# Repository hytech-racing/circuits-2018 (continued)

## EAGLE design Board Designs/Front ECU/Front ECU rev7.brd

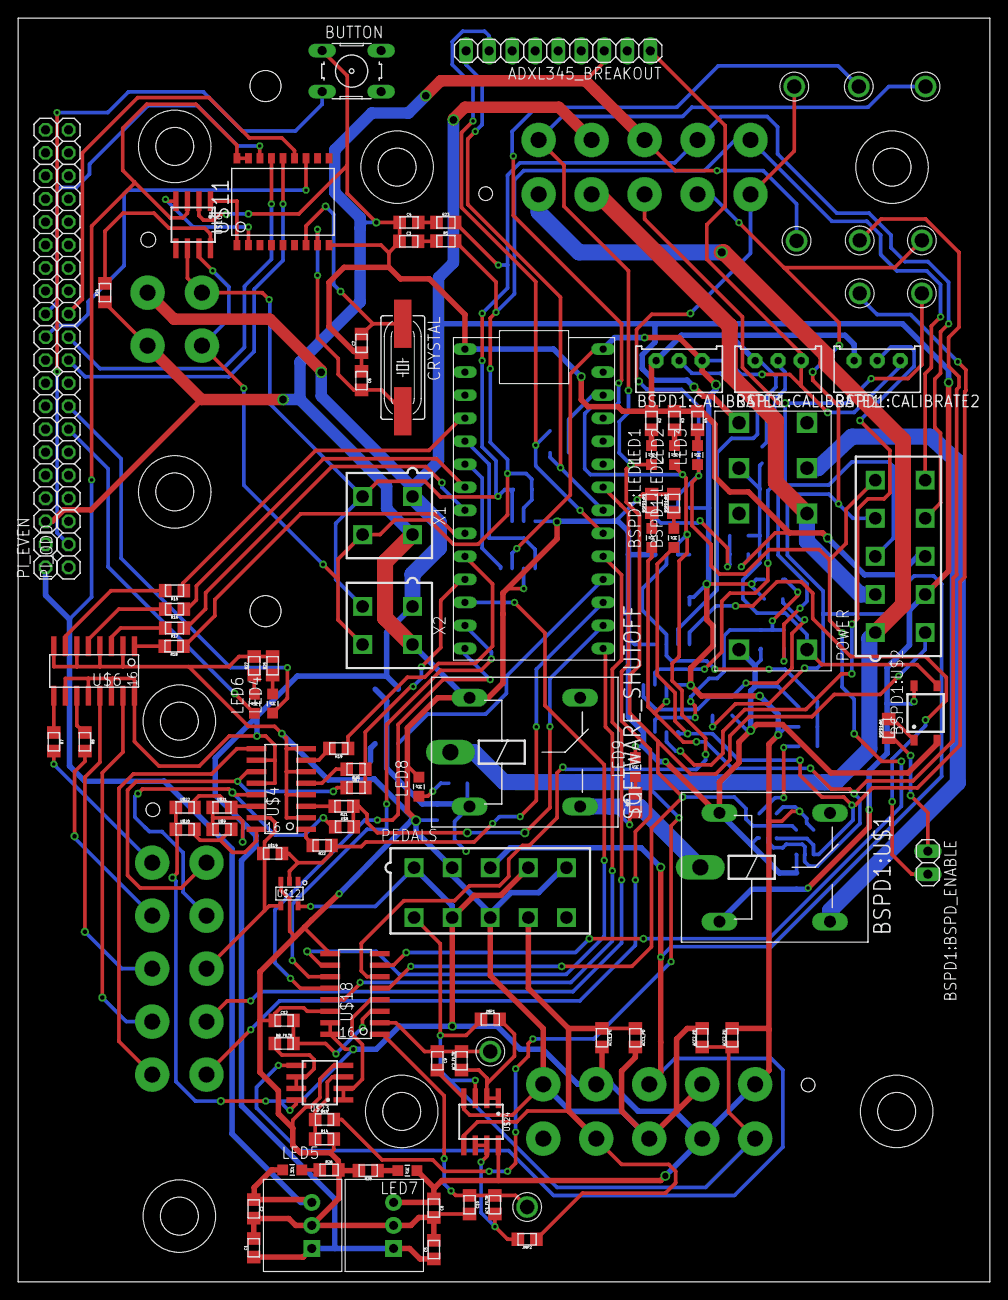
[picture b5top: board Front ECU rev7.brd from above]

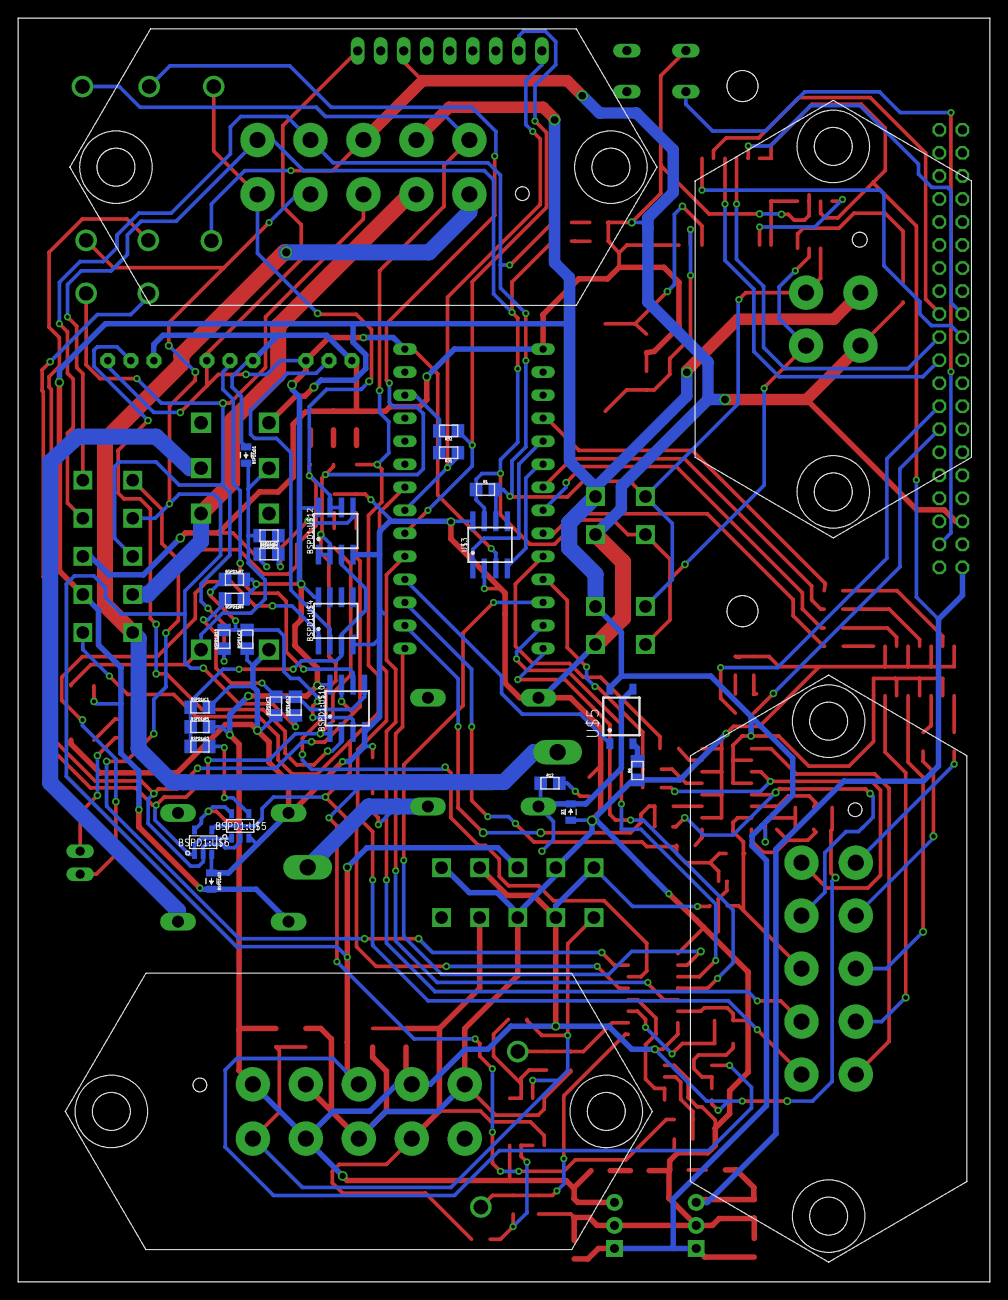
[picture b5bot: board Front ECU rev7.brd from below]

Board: 2 copper layers, 107.2 x 139.4 mm, 132 parts (30 on the bottom side), 107 nets.

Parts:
AC1_FILTR, AC2_FILTR: 510; 0805
ACC1_PD, ACC1_PU, ACC2_PD, ACC2_PU: 10k; 0805
ADXL345_BREAKOUT: 1X09
BR_FILTR: 100; 0805
BSPD1:BSPD_ENABLE: JUMPER; 1X02
BSPD1:C1: .47µ; 0805
BSPD1:C2, BSPD1:C3: 2.2µ; 0805
BSPD1:CALIBRATE1, BSPD1:CALIBRATE2, BSPD1:CALIBRATE3: TRIMPOT_3296
BSPD1:D1, BSPD1:D2: DIODE0805; 0805_D
BSPD1:LED1: RED; LED-805
BSPD1:LED2: YELLOW; LED-805
BSPD1:R1: 12k; 0805
BSPD1:R2: 43k; 0805
BSPD1:R3: 330; 0805
BSPD1:R4, BSPD1:R7: 10k; 0805
BSPD1:R5: 680k; 0805
BSPD1:R6: 680; 0805
BSPD1:R8, BSPD1:R9: 270; 0805
BSPD1:R10, BSPD1:R12: 100; 0805
BSPD1:U$1: G5LE; ZF112
BSPD1:U$2: CPC1002N; SOP04
BSPD1:U$3: JW2SN-DC12V; JW2SN
BSPD1:U$4, BSPD1:U$10: MCP6542SOIC; SOIC-08
BSPD1:U$5: SN74AHC1G09; SOT-23-5
BSPD1:U$6: SN74LVC1G08; SOT-23-5
BSPD1:U$11, BSPD1:U$13: TEST_POINT
BSPD1:U$12: MCP6002SOIC; SOIC-08
BUTTON: B3F-10XX
C1, C2, C5, C8: 10uF; 0805
C3, C4: 560pF; 0805
C6, C7: 22pF; 0805
C9, C10: 22µ; 0805
C12: 2.2µ; 0805
CRYSTAL: 16MHz; HC49UP
D3: DIODE0805; 0805_D
IC2, IC3: OKI-78SR
JMP1, JMP2: 0; 0805
LED1, LED6, LED8, LED9: RED; LED-805
LED2: YELLOW; LED-805
LED3, LED4: GREEN; LED-805
LED5, LED7: PURPLE; LED-805
PEDALS: MINIFIT_5566-10
PI_EVEN: 1X20
PI_ODD: 1X20
POWER: MINIFIT_5566-10
R1: 120; 0805
R2, R3, R15, R16, R17, R18, R19, R20, R21, R22, R27: 270; 0805
R4, R25, R26, R28: 200; 0805
R5, R23: 100; 0805
R6: 330; 0805
R7, R8: 0; 0805
R12, R29: 1.2K; 0805
R13: 43k; 0805
R14: 12k; 0805
R24, R31, R32: 4.7k; 0805
SOFTWARE_SHUTOFF: G5LE; ZF112
U$1: TEENSY_3.2_SIMPLE
U$2, U$13, U$14, U$15, U$16, U$17, U$25, U$26: TEST_POINT
U$3, U$10: MCP2551; SOIC-08
U$4, U$6: TLP291-4; SOIC-16
U$5: CPC1002N; SOP04
U$7, U$8, U$9, U$19, U$20, U$21, U$22: JUMPER; 0805
U$11: MCP2515SMD; SOIC-18W
U$12: SN74LV1T34; SOT-23-5
U$18: MCP3208SOIC; SOIC-16
U$23, U$24: MCP6002SOIC; SOIC-08
X1, X2: CONNECTOR-4; MINIFIT_5566-4
X3: CONNECTOR-4MX150L_VERTICAL-4; MX150L_VERTICAL-4
X4, X5, X6: CONNECTOR-10MX150L_VERTICAL-10; MX150L_VERTICAL-10

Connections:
3.3V+: R31.2, R32.2, U$1.3.3V
+5V: ACC1_PU.2, ACC2_PU.2, ADXL345_BREAKOUT.1, BSPD1:CALIBRATE1.1, BSPD1:CALIBRATE2.1, BSPD1:CALIBRATE3.1, BSPD1:R4.1, BSPD1:R5.2, BSPD1:R7.2, BSPD1:U$4.8, BSPD1:U$5.5, BSPD1:U$6.5, BSPD1:U$10.8, BSPD1:U$12.8, C8.1, IC3.3, LED7.A, PEDALS.1, PEDALS.4, PEDALS.7, U$1.VIN, U$3.3, U$12.5, U$18.15, U$18.16, U$20.1, U$22.1, U$23.8, U$24.8, X4.1, X4.4, X4.7
+5V/1: C2.1, IC2.3, LED5.A, PI_EVEN.1, U$10.3, U$11.17, U$11.18
+12V: BSPD1:D2.C, BSPD1:U$1.2, BSPD1:U$2.4, BSPD1:U$3.4, C1.1, C5.1, IC2.1, IC3.1, POWER.7, U$4.10, U$4.12, U$5.4, U$6.10, U$6.12, U$6.14, U$6.16, U$9.1, U$21.1, X1.1, X2.1, X3.1, X5.7
BSPD1:N$1: BSPD1:D1.C, BSPD1:R2.2, BSPD1:U$2.3, BSPD1:U$3.3, BSPD1:U$3.COIL-
BSPD1:N$2: BSPD1:R3.2, BSPD1:U$5.4
BSPD1:N$3: BSPD1:R6.2, BSPD1:U$2.1
BSPD1:N$4: BSPD1:BSPD_ENABLE.1, BSPD1:R6.1
BSPD1:N$5: BSPD1:CALIBRATE2.2, BSPD1:U$10.2
BSPD1:N$6: BSPD1:CALIBRATE1.2, BSPD1:U$10.6
BSPD1:N$7: BSPD1:CALIBRATE3.2, BSPD1:U$4.2
BSPD1:N$8: BSPD1:BSPD_ENABLE.2, BSPD1:U$4.1
BSPD1:N$9: BSPD1:R1.2, BSPD1:R2.1, BSPD1:U$12.5
BSPD1:N$13: BSPD1:C1.1, BSPD1:R3.1, BSPD1:R5.1, BSPD1:U$4.3, BSPD1:U$12.3
BSPD1:N$14: BSPD1:LED2.C, BSPD1:R8.1
BSPD1:N$15: BSPD1:LED1.C, BSPD1:R9.1
BSPD1:N$16: BSPD1:LED1.A, BSPD1:U$5.2, BSPD1:U$6.2, BSPD1:U$10.7, BSPD1:U$11.P$1
BSPD1:N$17: BSPD1:LED2.A, BSPD1:U$5.1, BSPD1:U$6.1, BSPD1:U$10.1, BSPD1:U$13.P$1
BSPD1:SHUTDOWN_C: BSPD1:U$1.S, BSPD1:U$3.6
BSPD1:SIGNAL_BRAKE_FILT: BSPD1:C3.2, BSPD1:R4.2, BSPD1:R12.2, BSPD1:U$10.5
BSPD1:SIGNAL_CURRENT_FILT: BSPD1:C2.2, BSPD1:R7.1, BSPD1:R10.2, BSPD1:U$10.3
BUT: BUTTON.3, PI_ODD.2
CANH: POWER.10, R1.1, R5.2, U$3.7, U$10.7, X1.4, X2.4, X3.4, X5.10
CANL: POWER.9, R1.2, R23.2, U$3.6, U$10.6, X1.3, X2.3, X3.3, X5.9
CS: PI_EVEN.12, U$11.16
CS_MCP3208: U$1.D10(TX2), U$18.10
DASH_CTRL1: R15.1, U$1.D2
DASH_CTRL2: R16.1, U$1.D5
DASH_CTRL3: R17.1, U$1.D6
DASH_CTRL4: R18.1, U$1.D7(RX3)
DASH_CTRL5: R19.1, U$1.D8(TX3)
DASH_CTRL6: R20.1, U$1.D9(RX2), U$7.2
DASH_CTRL7: R21.1, U$1.A0, U$8.2
DASH_CTRL8: R22.1, U$1.A1, U$12.2, U$19.2
DASH_CTRL9: U$1.A3, X6.9
DASH_CTRL10: U$1.A6, X6.10
DASH_IO1: R7.2, X6.1
DASH_IO2: R8.2, X6.2
DASH_IO3: U$6.13, X6.3
DASH_IO4: U$6.15, X6.4
DASH_IO5: U$4.9, X6.5
DASH_IO6: U$4.11, U$7.1, X6.6
DASH_IO7: U$4.13, U$8.1, X6.7
DASH_IO8: U$4.15, U$12.4, U$19.1, X6.8
GND: ACC1_PD.2, ACC2_PD.2, ADXL345_BREAKOUT.3, BSPD1:C1.2, BSPD1:C2.1, BSPD1:C3.1, BSPD1:CALIBRATE1.3, BSPD1:CALIBRATE2.3, BSPD1:CALIBRATE3.3, BSPD1:D1.A, BSPD1:D2.A, BSPD1:R1.1, BSPD1:R8.2, BSPD1:R9.2, BSPD1:U$1.1, BSPD1:U$2.2, BSPD1:U$3.COIL+, BSPD1:U$4.4, BSPD1:U$5.3, BSPD1:U$6.3, BSPD1:U$10.4, BSPD1:U$12.4, BUTTON.1, C1.2, C2.2, C3.1, C4.1, C5.2, C6.1, C7.1, C8.2, C9.2, C10.2, C12.1, D3.A, IC2.2, IC3.2, LED8.C, LED9.C, PEDALS.2, PEDALS.5, PEDALS.8, PI_EVEN.3, POWER.8, R2.1, R3.1, R4.1, R6.1, R14.2, R24.1, R25.2, R26.2, R27.2, R28.2, SOFTWARE_SHUTOFF.1, U$1.GND, U$2.P$1, U$3.2, U$3.8, U$4.2, U$4.4, U$4.6, U$4.8, U$6.2, U$6.4, U$6.6, U$6.8, U$10.2, U$11.9, U$12.3, U$18.9, U$18.14, U$23.4, U$24.4, X1.2, X2.2, X3.2, X4.2, X4.5, X4.8, X5.8
INT: PI_EVEN.11, U$11.12
LED1: LED4.A, PI_ODD.8
LED2: LED6.A, PI_ODD.7
MISO: PI_ODD.11, U$11.15
MISO_TEENSY: U$1.D12, U$18.12
MOSI: PI_ODD.10, U$11.14
MOSI_TEENSY: U$1.D11, U$18.11
unnamed: R7.1, U$6.9
unnamed: U$1.D4(CANRX), U$3.4
unnamed: R8.1, U$6.11
unnamed: U$4.16, U$9.2, U$20.2
unnamed: U$1.D3(CANTX), U$3.1
unnamed: U$4.14, U$21.2, U$22.2
unnamed: R13.1, R14.1, U$23.3
unnamed: LED8.A, R12.2
unnamed: LED9.A, R29.2
unnamed: BR_FILTR.1, U$23.6, U$23.7
unnamed: D3.C, R12.1, SOFTWARE_SHUTOFF.2, U$5.3
unnamed: AC2_FILTR.1, JMP1.2, U$24.1, U$24.2
unnamed: LED1.C, R2.2
unnamed: LED2.C, R3.2
unnamed: LED3.C, R4.2
unnamed: AC1_FILTR.1, JMP2.2, U$24.6, U$24.7
unnamed: R15.2, U$6.7
unnamed: R6.2, U$5.2
unnamed: R16.2, U$6.5
unnamed: R21.2, U$4.3
unnamed: R17.2, U$6.3
unnamed: R18.2, U$6.1
unnamed: R19.2, U$4.7
unnamed: R20.2, U$4.5
unnamed: R22.2, U$4.1
unnamed: U$10.1, U$11.1
unnamed: U$10.4, U$11.2
unnamed: C6.2, CRYSTAL.2, U$11.8
unnamed: R24.2, U$10.8
unnamed: C7.2, CRYSTAL.1, U$11.7
unnamed: C3.2, R5.1
unnamed: C4.2, R23.1
unnamed: LED4.C, R25.1
unnamed: LED5.C, R26.1
unnamed: LED6.C, R27.1
unnamed: LED7.C, R28.1
READ_ACCEL1: AC1_FILTR.2, C10.1, U$18.1, U$26.P$1
READ_ACCEL2: AC2_FILTR.2, C9.1, U$18.2, U$25.P$1
READ_BRAKE: BR_FILTR.2, C12.2, U$18.3
READ_CHARGE: BSPD1:U$12.1, BSPD1:U$12.2, LED2.A, U$16.P$1, U$18.6
READ_FAULT: BSPD1:U$12.6, BSPD1:U$12.7, LED3.A, POWER.5, U$15.P$1, U$18.7, X5.5
READ_SWITCH: BSPD1:U$6.4, LED1.A, POWER.6, U$17.P$1, U$18.5, X5.6
READ_UPSTREAM_SHUTDOWN: U$18.4, U$23.1, U$23.2
SCK: PI_ODD.12, U$11.13
SCK_TEENSY: U$1.D13, U$18.13
SCL: ADXL345_BREAKOUT.9, R31.1, U$1.A5
SDA: ADXL345_BREAKOUT.8, R32.1, U$1.A4
SHUTDOWN_A: POWER.1, R13.2, SOFTWARE_SHUTOFF.P, X5.1
SHUTDOWN_B: BSPD1:U$1.P, R29.1, SOFTWARE_SHUTOFF.S
SHUTDOWN_D: BSPD1:U$3.7, POWER.2, X5.2
SHUTDOWN_RELAY_CTRL: U$1.A2, U$5.1
SIGNAL_ACCEL1: ACC1_PD.1, ACC1_PU.1, JMP2.1, PEDALS.9, U$24.5, X4.9
SIGNAL_ACCEL2: ACC2_PD.1, ACC2_PU.1, JMP1.1, PEDALS.6, U$24.3, X4.6
SIGNAL_BRAKE: BSPD1:R12.1, PEDALS.3, POWER.4, U$13.P$1, U$23.5, X4.3, X5.4
SIGNAL_CURRENT: BSPD1:R10.1, POWER.3, U$14.P$1, X5.3

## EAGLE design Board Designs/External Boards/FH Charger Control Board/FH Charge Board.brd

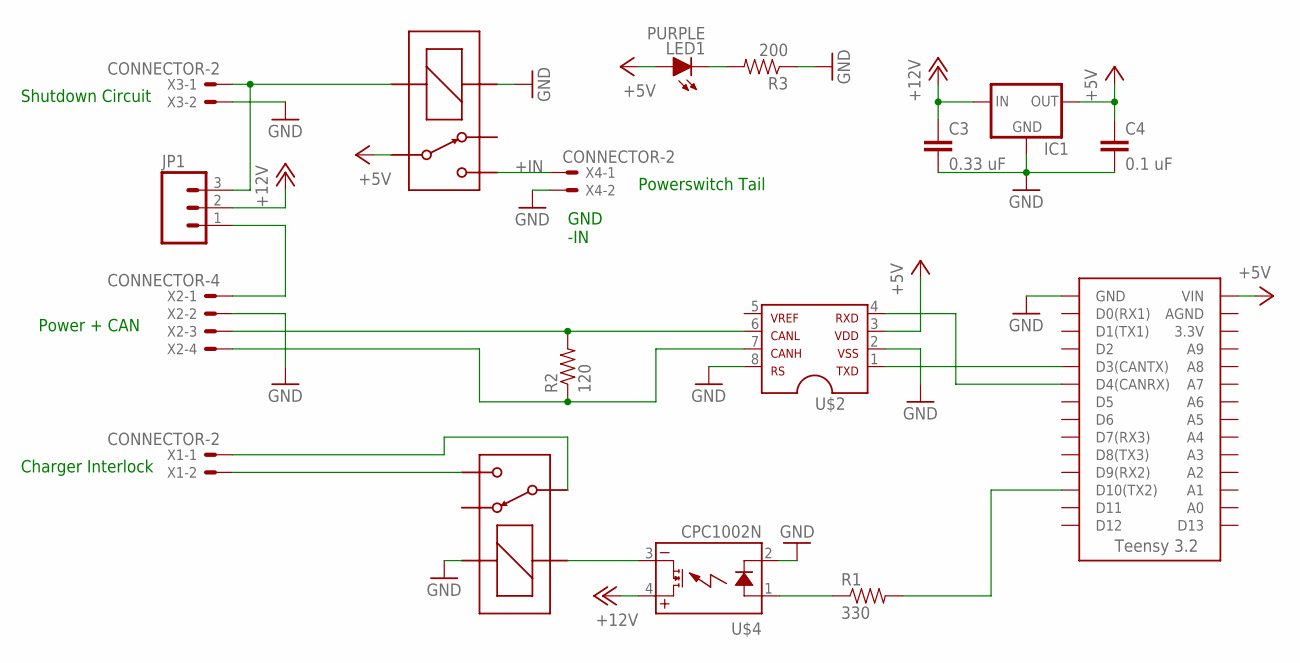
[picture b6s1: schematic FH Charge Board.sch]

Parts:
C3: 0.33 uF; 0805
C4: 0.1 uF; 0805
IC1: 5VREG_L7805SPACED; TO-220-SPACED
JP1: M03; 1X03
LED1: PURPLE; LED-805
R1: 330; 0805
R2: 120; 0805
R3: 200; 0805
U$1, U$5: G5LE; ZF112
U$2: MCP2551DIL; DIL08
U$3: TEENSY_3.2_SIMPLE
U$4: CPC1002N; SOP04
X1, X3, X4: CONNECTOR-2; MINIFIT_5566-2
X2: CONNECTOR-4; MINIFIT_5566-4

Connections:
+5V: C4.1, IC1.3 (OUT), LED1.A, U$1.P, U$2.3, U$3.VIN
+12V: C3.1, IC1.1 (IN), JP1.2, U$4.4 (DC+)
+IN: U$1.S, X4.1
CANH: R2.1, U$2.7, X2.4
CANL: R2.2, U$2.6, X2.3
GND: C3.2, C4.2, IC1.2 (GND), R3.1, U$1.1 (COIL+), U$2.2, U$2.8, U$3.GND, U$4.2 (CONTROL-), U$5.1 (COIL+), X2.2, X3.2, X4.2
unnamed: LED1.C, R3.2
unnamed: U$5.S, X1.2
unnamed: R1.2, U$3.D10(TX2)
unnamed: U$4.3 (DC-), U$5.2 (COIL-)
unnamed: R1.1, U$4.1 (CONTROL+)
unnamed: U$5.P, X1.1
POWER_CAN_12V: JP1.1, X2.1
SHUTDOWN_12V: JP1.3, U$1.2 (COIL-), X3.1
UC_CANRX: U$2.4, U$3.D4(CANRX)
UC_CANTX: U$2.1, U$3.D3(CANTX)

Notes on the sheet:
Power + CAN
Powerswitch Tail
Shutdown Circuit
Charger Interlock
GND -IN

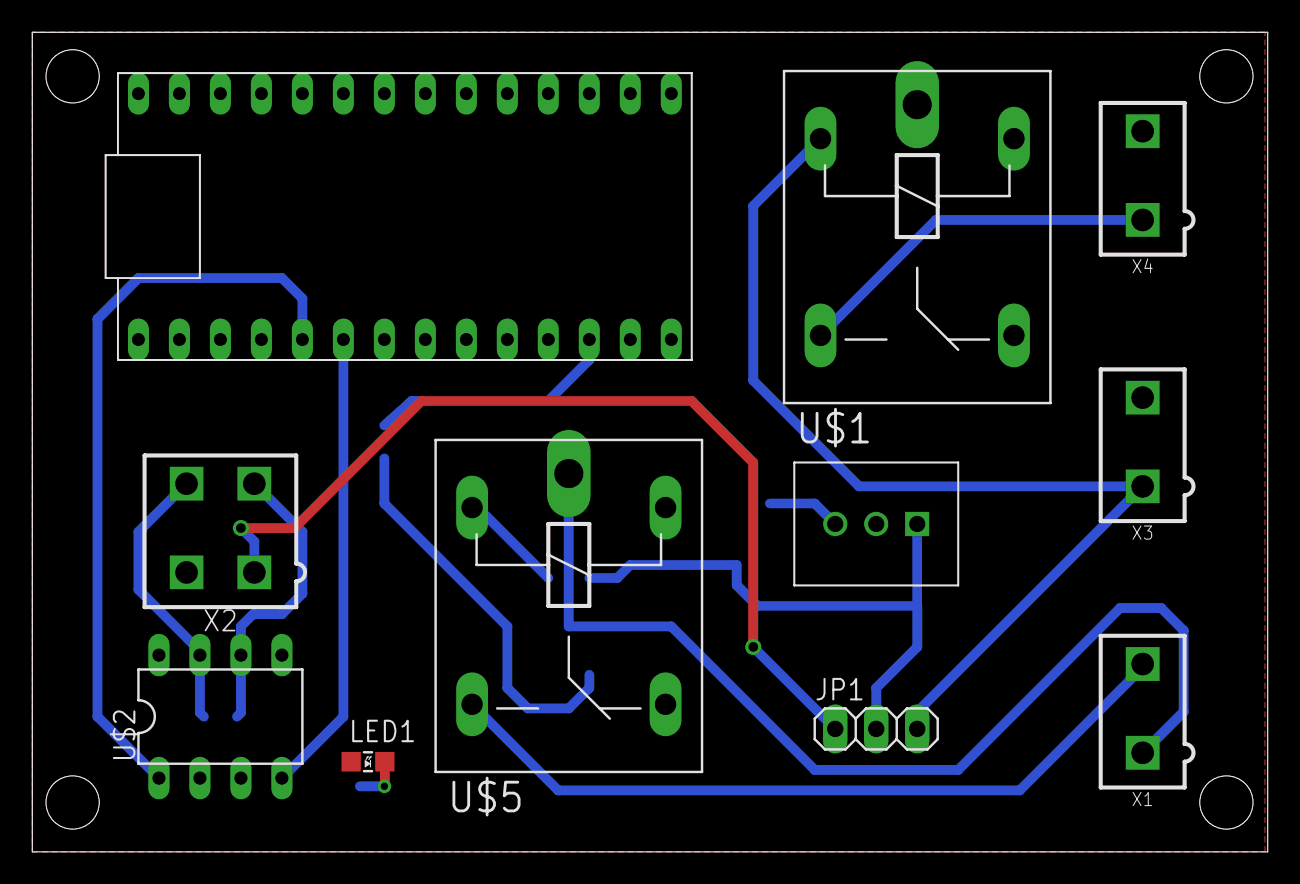
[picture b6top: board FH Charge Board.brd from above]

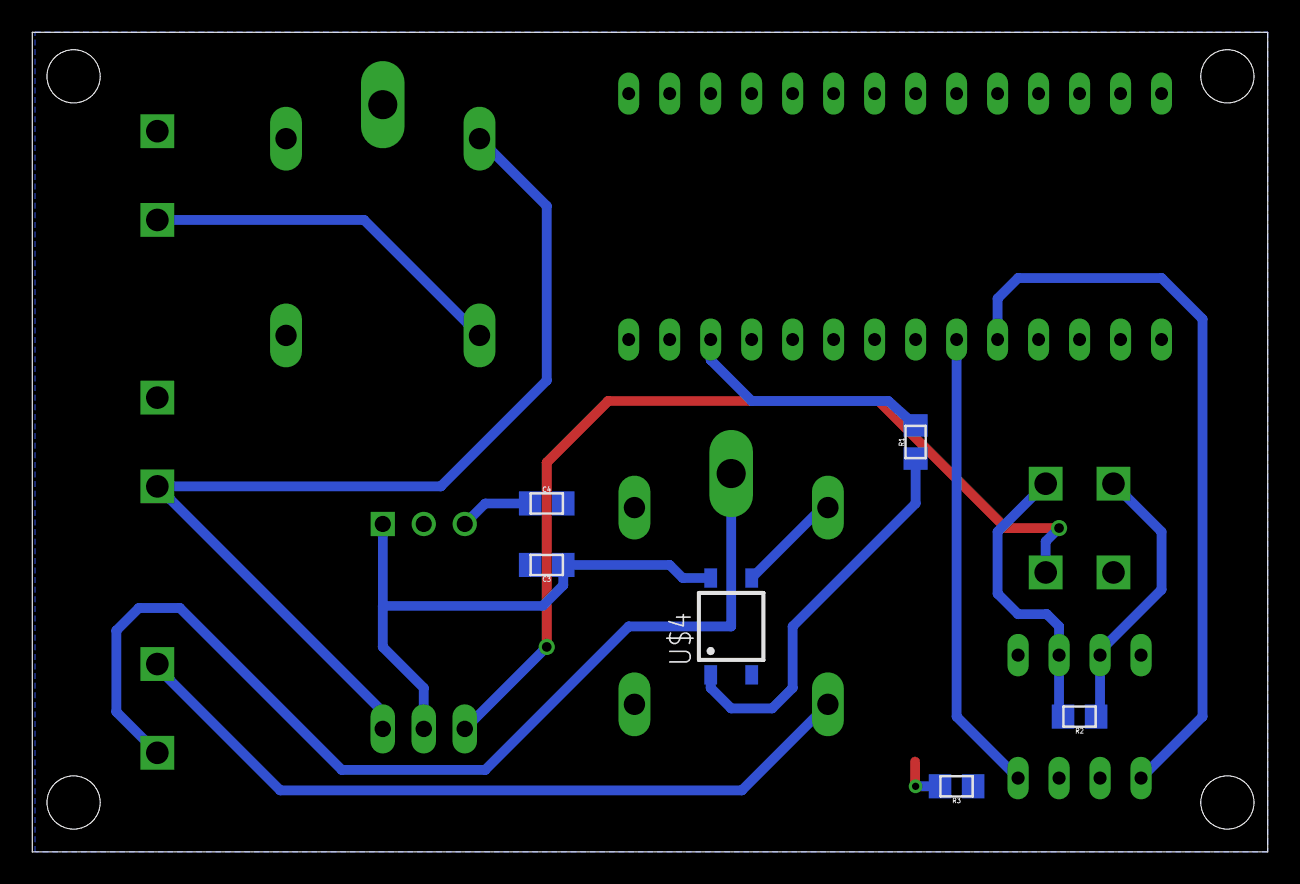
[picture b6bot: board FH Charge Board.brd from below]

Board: 2 copper layers, 76.6 x 50.8 mm, 17 parts (6 on the bottom side), 16 nets.

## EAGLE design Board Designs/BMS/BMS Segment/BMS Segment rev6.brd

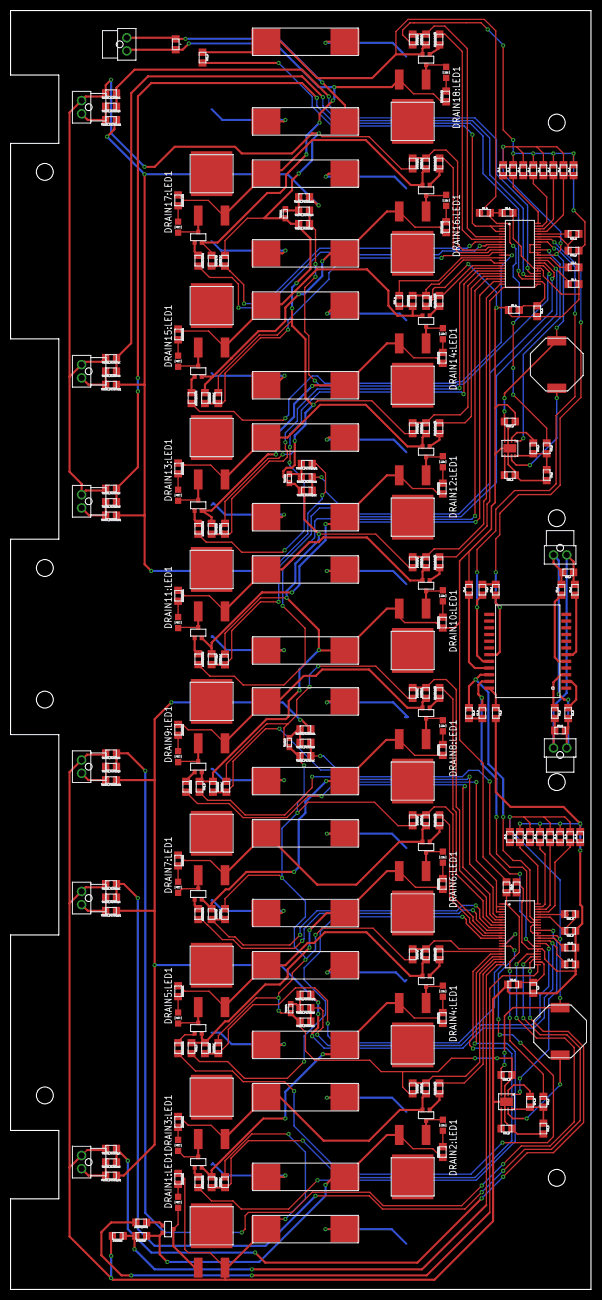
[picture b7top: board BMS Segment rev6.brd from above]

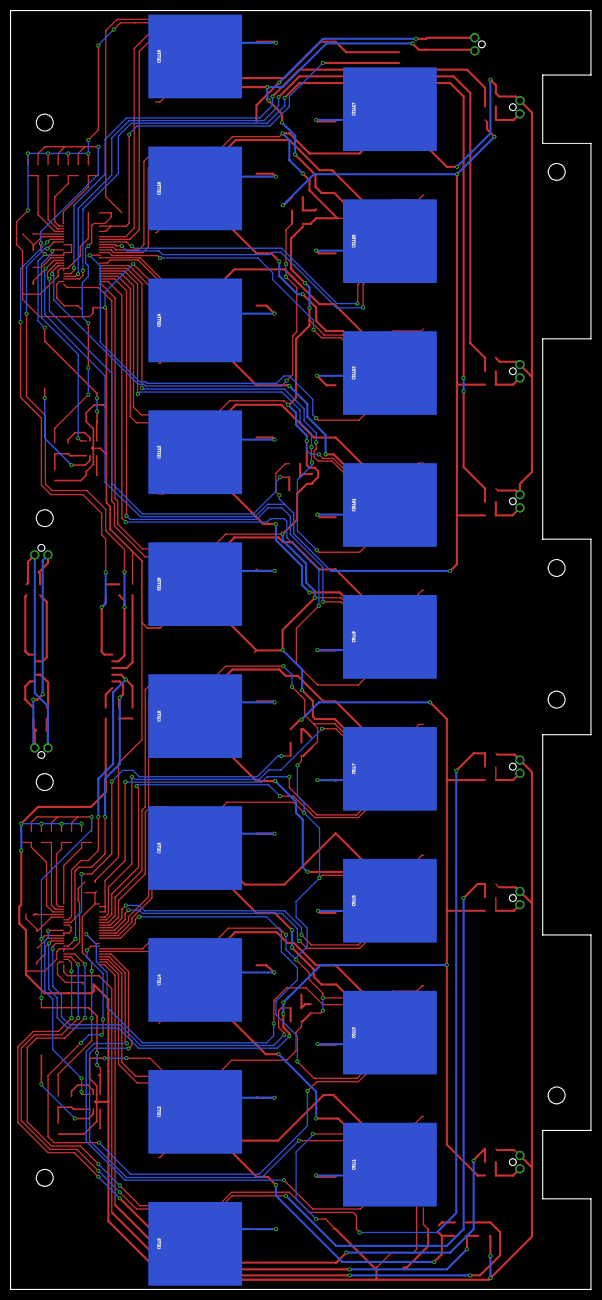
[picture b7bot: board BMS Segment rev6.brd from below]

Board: 2 copper layers, 110.0 x 242.3 mm, 273 parts (19 on the bottom side), 199 nets.

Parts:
AMS_TEST_PORT1: CONNECTOR-2NANO-FIT_VERTICAL-2; NANO-FIT_VERTICAL-2
BUCK_CONV_A: ADP2360; LFCSP-8
BUCK_CONV_B: ADP2360; LFCSP-8
C1_A, C1_B, C2_A, C2_B: 1uF; 0805
C3_A, C3_B: 15pF; 0805
C4_A, C4_B, C5_A: 10nF; 0805
C6_A, C6_B: 0.1uF; 0805
CELL0, CELL1, CELL2, CELL3, CELL4, CELL5, CELL6, CELL7, CELL8, CELL9, CELL10, CELL11, CELL12, CELL13, CELL14, CELL15, CELL16, CELL17, CELL18: BATTERY_SPRING_KEYSTONE5222; KEYSTONE5222
CIN_A: 4.7uF; 0805
CIN_B: 4.7uF; 0805
COUT_A: 22uF; 0805
COUT_B: 22uF; 0805
CSS_A: 2.2nF; 0805
CSS_B: 2.2nF; 0805
C_5: 10nF; 0805
DRAIN1:C, DRAIN2:C, DRAIN3:C, DRAIN4:C, DRAIN5:C, DRAIN6:C, DRAIN7:C, DRAIN8:C, DRAIN9:C, DRAIN10:C, DRAIN11:C, DRAIN12:C, DRAIN13:C, DRAIN14:C, DRAIN15:C, DRAIN16:C, DRAIN17:C, DRAIN18:C: 10nF; 0805
DRAIN1:DISCHARGE, DRAIN2:DISCHARGE, DRAIN3:DISCHARGE, DRAIN4:DISCHARGE, DRAIN5:DISCHARGE, DRAIN6:DISCHARGE, DRAIN7:DISCHARGE, DRAIN8:DISCHARGE, DRAIN9:DISCHARGE, DRAIN10:DISCHARGE, DRAIN11:DISCHARGE, DRAIN12:DISCHARGE, DRAIN13:DISCHARGE, DRAIN14:DISCHARGE, DRAIN15:DISCHARGE, DRAIN16:DISCHARGE, DRAIN17:DISCHARGE, DRAIN18:DISCHARGE: 5Ω; PWR163
DRAIN1:GATE, DRAIN2:GATE, DRAIN3:GATE, DRAIN4:GATE, DRAIN5:GATE, DRAIN6:GATE, DRAIN7:GATE, DRAIN8:GATE, DRAIN9:GATE, DRAIN10:GATE, DRAIN11:GATE, DRAIN12:GATE, DRAIN13:GATE, DRAIN14:GATE, DRAIN15:GATE, DRAIN16:GATE, DRAIN17:GATE, DRAIN18:GATE: 3.3kΩ; 0805
DRAIN1:LED1, DRAIN2:LED1, DRAIN3:LED1, DRAIN4:LED1, DRAIN5:LED1, DRAIN6:LED1, DRAIN7:LED1, DRAIN8:LED1, DRAIN9:LED1, DRAIN10:LED1, DRAIN11:LED1, DRAIN12:LED1, DRAIN13:LED1, DRAIN14:LED1, DRAIN15:LED1, DRAIN16:LED1, DRAIN17:LED1, DRAIN18:LED1: RED; LED-805
DRAIN1:PFET, DRAIN2:PFET, DRAIN3:PFET, DRAIN4:PFET, DRAIN5:PFET, DRAIN6:PFET, DRAIN7:PFET, DRAIN8:PFET, DRAIN9:PFET, DRAIN10:PFET, DRAIN11:PFET, DRAIN12:PFET, DRAIN13:PFET, DRAIN14:PFET, DRAIN15:PFET, DRAIN16:PFET, DRAIN17:PFET, DRAIN18:PFET: P-CHANNEL_MOSFET_DMP3099L-7; SOT23
DRAIN1:R, DRAIN2:R, DRAIN3:R, DRAIN4:R, DRAIN5:R, DRAIN6:R, DRAIN7:R, DRAIN8:R, DRAIN9:R, DRAIN10:R, DRAIN11:R, DRAIN12:R, DRAIN13:R, DRAIN14:R, DRAIN15:R, DRAIN16:R, DRAIN17:R, DRAIN18:R: 100Ω; 0805
DRAIN1:R1, DRAIN2:R1, DRAIN3:R1, DRAIN4:R1, DRAIN5:R1, DRAIN6:R1, DRAIN7:R1, DRAIN8:R1, DRAIN9:R1, DRAIN10:R1, DRAIN11:R1, DRAIN12:R1, DRAIN13:R1, DRAIN14:R1, DRAIN15:R1, DRAIN16:R1, DRAIN17:R1, DRAIN18:R1: 150; 0805
F0, F1, F2, F3, F4, F5, F6, F7, F8, F9, F10, F11, F12, F13, F14, F15, F16, F17, F18: 0001.2704.11; 5X20MM_FUSE
ISOSPI_A: CONNECTOR-2NANO-FIT_VERTICAL-2; NANO-FIT_VERTICAL-2
ISOSPI_B: CONNECTOR-2NANO-FIT_VERTICAL-2; NANO-FIT_VERTICAL-2
J, J1_A, J1_B, J2_A, J2_B, J3_A, J3_B, J4_A, J4_B, J5_A, J5_B, J6_A, J6_B, J7_A, J7_B, J8_A, J8_B: 0805
L1_A, L1_B: 330uH; SRU1048
R1_A, R1_B, R2_A, R2_B: 100Ω; 0805
R3_A, R3_B: 402Ω; 0805
R4_A, R4_B, R5_A, R5_B: 22Ω; 0805
RB1_A, RB1_B: 1.2kΩ; 0805
RB2_A, RB2_B: 800Ω; 0805
RIN_A: 1kΩ; 0805
RIN_B: 1kΩ; 0805
RM_A: 100Ω; 0805
RM_B: 100Ω; 0805
RPG_A: 10MΩ; 0805
RPG_B: 10MΩ; 0805
RU1_A, RU1_B, RU2_A, RU2_B: 100Ω; 0805
THERM1, THERM2, THERM3, THERM4: 10kΩ; 0603
THERM1_A, THERM1_B, THERM2_A, THERM2_B, THERM3_A, THERM3_B: Th1; NANO-FIT_VERTICAL-2
THERM_FILTER1:C, THERM_FILTER2:C, THERM_FILTER3:C, THERM_FILTER4:C, THERM_FILTER5:C, THERM_FILTER6:C, THERM_FILTER7:C, THERM_FILTER8:C, THERM_FILTER9:C, THERM_FILTER10:C: 10nF; 0805
THERM_FILTER1:R, THERM_FILTER2:R, THERM_FILTER3:R, THERM_FILTER4:R, THERM_FILTER5:R, THERM_FILTER6:R, THERM_FILTER7:R, THERM_FILTER8:R, THERM_FILTER9:R, THERM_FILTER10:R: 100Ω; 0805
THERM_FILTER1:R1, THERM_FILTER2:R1, THERM_FILTER3:R1, THERM_FILTER4:R1, THERM_FILTER5:R1, THERM_FILTER6:R1, THERM_FILTER7:R1, THERM_FILTER8:R1, THERM_FILTER9:R1, THERM_FILTER10:R1: 10kΩ; 0805
TRANSFORMER: SM51589PEL
U$1, U$2: LTC6804-2; LTC6804

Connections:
C0_A: C5_A.1, R2_A.2, U$1.26
C0_B: C_5.1, R2_B.2, U$2.26
C1_A: DRAIN10:C.1, DRAIN10:R.2, U$1.24
C1_B: DRAIN1:C.1, DRAIN1:R.2, U$2.24
C2_A: DRAIN11:C.1, DRAIN11:R.2, U$1.22
C2_B: DRAIN2:C.1, DRAIN2:R.2, U$2.22
C3_A: DRAIN12:C.1, DRAIN12:R.2, U$1.20
C3_B: DRAIN3:C.1, DRAIN3:R.2, U$2.20
C4_A: DRAIN13:C.1, DRAIN13:R.2, U$1.18
C4_B: DRAIN4:C.1, DRAIN4:R.2, U$2.18
C5_A: DRAIN14:C.1, DRAIN14:R.2, U$1.16
C5_B: DRAIN5:C.1, DRAIN5:R.2, U$2.16
C7_A: DRAIN15:C.1, DRAIN15:R.2, U$1.12
C7_B: DRAIN6:C.1, DRAIN6:R.2, U$2.12
C8_A: DRAIN16:C.1, DRAIN16:R.2, U$1.10
C8_B: DRAIN7:C.1, DRAIN7:R.2, U$2.10
C9_A: DRAIN17:C.1, DRAIN17:R.2, U$1.8
C9_B: DRAIN8:C.1, DRAIN8:R.2, U$2.8
C10_A: DRAIN18:C.1, DRAIN18:R.2, U$1.6
C10_B: DRAIN9:C.1, DRAIN9:R.2, U$2.6
CC0: CELL0.P$1, F0.P$1
CC1: CELL1.P$1, F1.P$1
CC2: CELL2.P$1, F2.P$1
CC3: CELL3.P$1, F3.P$1
CC4: CELL4.P$1, F4.P$1
CC5: CELL5.P$1, F5.P$1
CC6: CELL6.P$1, F6.P$1
CC7: CELL7.P$1, F7.P$1
CC8: CELL8.P$1, F8.P$1
CC9: CELL9.P$1, F9.P$1
CC10: CELL10.P$1, F10.P$1
CC11: CELL11.P$1, F11.P$1
CC12: CELL12.P$1, F12.P$1
CC13: CELL13.P$1, F13.P$1
CC14: CELL14.P$1, F14.P$1
CC15: CELL15.P$1, F15.P$1
CC16: CELL16.P$1, F16.P$1
CC17: CELL17.P$1, F17.P$1
CC18: CELL18.P$1, F18.P$1
DRAIN1:GATE: DRAIN1:GATE.1, DRAIN1:PFET.1
DRAIN1:N$1: DRAIN1:DISCHARGE.1, DRAIN1:LED1.A, DRAIN1:PFET.3
DRAIN1:N$2: DRAIN1:LED1.C, DRAIN1:R1.2
DRAIN2:GATE: DRAIN2:GATE.1, DRAIN2:PFET.1
DRAIN2:N$1: DRAIN2:DISCHARGE.1, DRAIN2:LED1.A, DRAIN2:PFET.3
DRAIN2:N$2: DRAIN2:LED1.C, DRAIN2:R1.2
DRAIN3:GATE: DRAIN3:GATE.1, DRAIN3:PFET.1
DRAIN3:N$1: DRAIN3:DISCHARGE.1, DRAIN3:LED1.A, DRAIN3:PFET.3
DRAIN3:N$2: DRAIN3:LED1.C, DRAIN3:R1.2
DRAIN4:GATE: DRAIN4:GATE.1, DRAIN4:PFET.1
DRAIN4:N$1: DRAIN4:DISCHARGE.1, DRAIN4:LED1.A, DRAIN4:PFET.3
DRAIN4:N$2: DRAIN4:LED1.C, DRAIN4:R1.2
DRAIN5:GATE: DRAIN5:GATE.1, DRAIN5:PFET.1
DRAIN5:N$1: DRAIN5:DISCHARGE.1, DRAIN5:LED1.A, DRAIN5:PFET.3
DRAIN5:N$2: DRAIN5:LED1.C, DRAIN5:R1.2
DRAIN6:GATE: DRAIN6:GATE.1, DRAIN6:PFET.1
DRAIN6:N$1: DRAIN6:DISCHARGE.1, DRAIN6:LED1.A, DRAIN6:PFET.3
DRAIN6:N$2: DRAIN6:LED1.C, DRAIN6:R1.2
DRAIN7:GATE: DRAIN7:GATE.1, DRAIN7:PFET.1
DRAIN7:N$1: DRAIN7:DISCHARGE.1, DRAIN7:LED1.A, DRAIN7:PFET.3
DRAIN7:N$2: DRAIN7:LED1.C, DRAIN7:R1.2
DRAIN8:GATE: DRAIN8:GATE.1, DRAIN8:PFET.1
DRAIN8:N$1: DRAIN8:DISCHARGE.1, DRAIN8:LED1.A, DRAIN8:PFET.3
DRAIN8:N$2: DRAIN8:LED1.C, DRAIN8:R1.2
DRAIN9:GATE: DRAIN9:GATE.1, DRAIN9:PFET.1
DRAIN9:N$1: DRAIN9:DISCHARGE.1, DRAIN9:LED1.A, DRAIN9:PFET.3
DRAIN9:N$2: DRAIN9:LED1.C, DRAIN9:R1.2
DRAIN10:GATE: DRAIN10:GATE.1, DRAIN10:PFET.1
DRAIN10:N$1: DRAIN10:DISCHARGE.1, DRAIN10:LED1.A, DRAIN10:PFET.3
DRAIN10:N$2: DRAIN10:LED1.C, DRAIN10:R1.2
DRAIN11:GATE: DRAIN11:GATE.1, DRAIN11:PFET.1
DRAIN11:N$1: DRAIN11:DISCHARGE.1, DRAIN11:LED1.A, DRAIN11:PFET.3
DRAIN11:N$2: DRAIN11:LED1.C, DRAIN11:R1.2
DRAIN12:GATE: DRAIN12:GATE.1, DRAIN12:PFET.1
DRAIN12:N$1: DRAIN12:DISCHARGE.1, DRAIN12:LED1.A, DRAIN12:PFET.3
DRAIN12:N$2: DRAIN12:LED1.C, DRAIN12:R1.2
DRAIN13:GATE: DRAIN13:GATE.1, DRAIN13:PFET.1
DRAIN13:N$1: DRAIN13:DISCHARGE.1, DRAIN13:LED1.A, DRAIN13:PFET.3
DRAIN13:N$2: DRAIN13:LED1.C, DRAIN13:R1.2
DRAIN14:GATE: DRAIN14:GATE.1, DRAIN14:PFET.1
DRAIN14:N$1: DRAIN14:DISCHARGE.1, DRAIN14:LED1.A, DRAIN14:PFET.3
DRAIN14:N$2: DRAIN14:LED1.C, DRAIN14:R1.2
DRAIN15:GATE: DRAIN15:GATE.1, DRAIN15:PFET.1
DRAIN15:N$1: DRAIN15:DISCHARGE.1, DRAIN15:LED1.A, DRAIN15:PFET.3
DRAIN15:N$2: DRAIN15:LED1.C, DRAIN15:R1.2
DRAIN16:GATE: DRAIN16:GATE.1, DRAIN16:PFET.1
DRAIN16:N$1: DRAIN16:DISCHARGE.1, DRAIN16:LED1.A, DRAIN16:PFET.3
DRAIN16:N$2: DRAIN16:LED1.C, DRAIN16:R1.2
DRAIN17:GATE: DRAIN17:GATE.1, DRAIN17:PFET.1
DRAIN17:N$1: DRAIN17:DISCHARGE.1, DRAIN17:LED1.A, DRAIN17:PFET.3
DRAIN17:N$2: DRAIN17:LED1.C, DRAIN17:R1.2
DRAIN18:GATE: DRAIN18:GATE.1, DRAIN18:PFET.1
DRAIN18:N$1: DRAIN18:DISCHARGE.1, DRAIN18:LED1.A, DRAIN18:PFET.3
DRAIN18:N$2: DRAIN18:LED1.C, DRAIN18:R1.2
DRIVE_A: BUCK_CONV_A.1, U$1.38
DRIVE_B: BUCK_CONV_B.1, U$2.38
GPIO1_A: THERM_FILTER6:C.1, THERM_FILTER6:R.1, U$1.27
GPIO1_B: THERM_FILTER1:C.1, THERM_FILTER1:R.1, U$2.27
GPIO2_A: THERM_FILTER7:C.1, THERM_FILTER7:R.1, U$1.28
GPIO2_B: THERM_FILTER2:C.1, THERM_FILTER2:R.1, U$2.28
GPIO3_A: THERM_FILTER8:C.1, THERM_FILTER8:R.1, U$1.29
GPIO3_B: THERM_FILTER3:C.1, THERM_FILTER3:R.1, U$2.29
GPIO4_A: THERM_FILTER9:C.1, THERM_FILTER9:R.1, U$1.32
GPIO4_B: THERM_FILTER4:C.1, THERM_FILTER4:R.1, U$2.32
GPIO5_A: THERM_FILTER10:C.1, THERM_FILTER10:R.1, U$1.33
GPIO5_B: THERM_FILTER5:C.1, THERM_FILTER5:R.1, U$2.33
IM_A: C3_A.2, TRANSFORMER.20, U$1.41
IM_B: C3_B.2, TRANSFORMER.23, U$2.41
IP_A: R3_A.1, TRANSFORMER.19, U$1.42
IP_B: R3_B.1, TRANSFORMER.22, U$2.42
ISOSPI-M: ISOSPI_A.P$2, ISOSPI_B.P$2, R5_A.2, R5_B.2, RM_A.2, RM_B.2
ISOSPI-P: ISOSPI_A.P$1, ISOSPI_B.P$1, R4_A.2, R4_B.2, RM_A.1, RM_B.1
unnamed: C4_B.1, TRANSFORMER.24
unnamed: RB1_B.2, U$2.44
unnamed: THERM1_B.P$1, THERM_FILTER1:R.2, THERM_FILTER1:R1.2
unnamed: RB1_B.1, RB2_B.2, U$2.43
unnamed: R4_B.1, TRANSFORMER.3
unnamed: RB1_A.2, U$1.44
unnamed: R5_B.1, TRANSFORMER.2
unnamed: J7_B.1, J8_B.1, U$2.48
unnamed: J5_B.1, J6_B.1, U$2.47
unnamed: C3_B.1, R3_B.2
unnamed: BUCK_CONV_B.8, CIN_B.1, RIN_B.2, RPG_B.2
unnamed: BUCK_CONV_B.2, RPG_B.1
unnamed: J3_B.1, J4_B.1, U$2.46
unnamed: BUCK_CONV_B.5, CSS_B.2
unnamed: BUCK_CONV_B.7, L1_B.1
unnamed: J1_B.1, J2_B.1, U$2.45
unnamed: THERM4.2, THERM_FILTER5:R.2, THERM_FILTER5:R1.2
unnamed: THERM2_B.P$1, THERM_FILTER2:R.2, THERM_FILTER2:R1.2
unnamed: THERM3.2, THERM_FILTER4:R.2, THERM_FILTER4:R1.2
unnamed: RB1_A.1, RB2_A.2, U$1.43
unnamed: C4_A.1, TRANSFORMER.21
unnamed: R4_A.1, TRANSFORMER.6
unnamed: R5_A.1, TRANSFORMER.5
unnamed: C3_A.1, R3_A.2
unnamed: BUCK_CONV_A.8, CIN_A.1, RIN_A.2, RPG_A.2
unnamed: THERM3_B.P$1, THERM_FILTER3:R.2, THERM_FILTER3:R1.2
unnamed: BUCK_CONV_A.2, RPG_A.1
unnamed: BUCK_CONV_A.5, CSS_A.2
unnamed: BUCK_CONV_A.7, L1_A.1
unnamed: J7_A.1, J8_A.1, U$1.48
unnamed: J5_A.1, J6_A.1, U$1.47
unnamed: J3_A.1, J4_A.1, U$1.46
unnamed: J1_A.1, J2_A.1, U$1.45
unnamed: THERM1.2, THERM_FILTER9:R.2, THERM_FILTER9:R1.2
unnamed: THERM3_A.P$1, THERM_FILTER8:R.2, THERM_FILTER8:R1.2
unnamed: THERM2.2, THERM_FILTER10:R.2, THERM_FILTER10:R1.2
unnamed: THERM2_A.P$1, THERM_FILTER7:R.2, THERM_FILTER7:R1.2
unnamed: THERM1_A.P$1, THERM_FILTER6:R.2, THERM_FILTER6:R1.2
S1_A: DRAIN10:GATE.2, U$1.25
S1_B: DRAIN1:GATE.2, U$2.25
S2_A: DRAIN11:GATE.2, U$1.23
S2_B: DRAIN2:GATE.2, U$2.23
S3_A: DRAIN12:GATE.2, U$1.21
S3_B: DRAIN3:GATE.2, U$2.21
S4_A: DRAIN13:GATE.2, U$1.19
S4_B: DRAIN4:GATE.2, U$2.19
S5_A: DRAIN14:GATE.2, U$1.17
S5_B: DRAIN5:GATE.2, U$2.17
S7_A: DRAIN15:GATE.2, U$1.13
S7_B: DRAIN6:GATE.2, U$2.13
S8_A: DRAIN16:GATE.2, U$1.11
S8_B: DRAIN7:GATE.2, U$2.11
S9_A: DRAIN17:GATE.2, U$1.9
S9_B: DRAIN8:GATE.2, U$2.9
S10_A: DRAIN18:GATE.2, U$1.7
S10_B: DRAIN9:GATE.2, U$2.7
SENSE1: DRAIN1:PFET.2, DRAIN1:R.1, DRAIN2:DISCHARGE.2, DRAIN2:R1.1, F1.P$2
SENSE2: DRAIN2:PFET.2, DRAIN2:R.1, DRAIN3:DISCHARGE.2, DRAIN3:R1.1, F2.P$2
SENSE3: DRAIN3:PFET.2, DRAIN3:R.1, DRAIN4:DISCHARGE.2, DRAIN4:R1.1, F3.P$2
SENSE4: DRAIN4:PFET.2, DRAIN4:R.1, DRAIN5:DISCHARGE.2, DRAIN5:R1.1, F4.P$2
SENSE5: DRAIN5:PFET.2, DRAIN5:R.1, DRAIN6:DISCHARGE.2, DRAIN6:R1.1, F5.P$2, RU2_B.1
SENSE6: DRAIN6:PFET.2, DRAIN6:R.1, DRAIN7:DISCHARGE.2, DRAIN7:R1.1, F6.P$2
SENSE7: DRAIN7:PFET.2, DRAIN7:R.1, DRAIN8:DISCHARGE.2, DRAIN8:R1.1, F7.P$2
SENSE8: DRAIN8:PFET.2, DRAIN8:R.1, DRAIN9:DISCHARGE.2, DRAIN9:R1.1, F8.P$2
SENSE10: DRAIN10:PFET.2, DRAIN10:R.1, DRAIN11:DISCHARGE.2, DRAIN11:R1.1, F10.P$2
SENSE11: DRAIN11:PFET.2, DRAIN11:R.1, DRAIN12:DISCHARGE.2, DRAIN12:R1.1, F11.P$2
SENSE12: DRAIN12:PFET.2, DRAIN12:R.1, DRAIN13:DISCHARGE.2, DRAIN13:R1.1, F12.P$2
SENSE13: DRAIN13:PFET.2, DRAIN13:R.1, DRAIN14:DISCHARGE.2, DRAIN14:R1.1, F13.P$2
SENSE14: DRAIN14:PFET.2, DRAIN14:R.1, DRAIN15:DISCHARGE.2, DRAIN15:R1.1, F14.P$2, RU2_A.1
SENSE15: DRAIN15:PFET.2, DRAIN15:R.1, DRAIN16:DISCHARGE.2, DRAIN16:R1.1, F15.P$2
SENSE16: DRAIN16:PFET.2, DRAIN16:R.1, DRAIN17:DISCHARGE.2, DRAIN17:R1.1, F16.P$2
SENSE17: AMS_TEST_PORT1.P$2, DRAIN17:PFET.2, DRAIN17:R.1, DRAIN18:DISCHARGE.2, DRAIN18:R1.1, J.2
SENSE17_J: AMS_TEST_PORT1.P$1, F17.P$2, J.1
SENSE18: DRAIN18:PFET.2, DRAIN18:R.1, F18.P$2, R1_A.1, RU1_A.1
UNUSED1_A: RU1_A.2, U$1.2, U$1.4
UNUSED1_B: RU1_B.2, U$2.2, U$2.4
UNUSED2_A: RU2_A.2, U$1.14
UNUSED2_B: RU2_B.2, U$2.14
V+_A: C6_A.1, R1_A.2, RIN_A.1, U$1.1
V+_B: C6_B.1, R1_B.2, RIN_B.1, U$2.1
V-_A: BUCK_CONV_A.3, BUCK_CONV_A.6, BUCK_CONV_A.PAD, C1_A.2, C2_A.2, C4_A.2, C5_A.2, C6_A.2, CIN_A.2, COUT_A.1, CSS_A.1, DRAIN9:PFET.2, DRAIN9:R.1, DRAIN10:C.2, DRAIN10:DISCHARGE.2, DRAIN10:R1.1, DRAIN11:C.2, DRAIN12:C.2, DRAIN13:C.2, DRAIN14:C.2, DRAIN15:C.2, DRAIN16:C.2, DRAIN17:C.2, DRAIN18:C.2, F9.P$2, J1_A.2, J3_A.2, J5_A.2, J7_A.2, R1_B.1, R2_A.1, RB2_A.1, RU1_B.1, THERM1.1, THERM1_A.P$2, THERM2.1, THERM2_A.P$2, THERM3_A.P$2, THERM_FILTER6:C.2, THERM_FILTER7:C.2, THERM_FILTER8:C.2, THERM_FILTER9:C.2, THERM_FILTER10:C.2, U$1.30, U$1.31
V-_B: BUCK_CONV_B.3, BUCK_CONV_B.6, BUCK_CONV_B.PAD, C1_B.2, C2_B.2, C4_B.2, C6_B.2, CIN_B.2, COUT_B.1, CSS_B.1, C_5.2, DRAIN1:C.2, DRAIN1:DISCHARGE.2, DRAIN1:R1.1, DRAIN2:C.2, DRAIN3:C.2, DRAIN4:C.2, DRAIN5:C.2, DRAIN6:C.2, DRAIN7:C.2, DRAIN8:C.2, DRAIN9:C.2, F0.P$2, J1_B.2, J3_B.2, J5_B.2, J7_B.2, R2_B.1, RB2_B.1, THERM1_B.P$2, THERM2_B.P$2, THERM3.1, THERM3_B.P$2, THERM4.1, THERM_FILTER1:C.2, THERM_FILTER2:C.2, THERM_FILTER3:C.2, THERM_FILTER4:C.2, THERM_FILTER5:C.2, U$2.30, U$2.31
VREF1_A: C2_A.1, U$1.35
VREF1_B: C2_B.1, U$2.35
VREF2_A: C1_A.1, THERM_FILTER6:R1.1, THERM_FILTER7:R1.1, THERM_FILTER8:R1.1, THERM_FILTER9:R1.1, THERM_FILTER10:R1.1, U$1.34
VREF2_B: C1_B.1, THERM_FILTER1:R1.1, THERM_FILTER2:R1.1, THERM_FILTER3:R1.1, THERM_FILTER4:R1.1, THERM_FILTER5:R1.1, U$2.34
VREG_A: BUCK_CONV_A.4, COUT_A.2, J2_A.2, J4_A.2, J6_A.2, J8_A.2, L1_A.2, U$1.36, U$1.37, U$1.40
VREG_B: BUCK_CONV_B.4, COUT_B.2, J2_B.2, J4_B.2, J6_B.2, J8_B.2, L1_B.2, U$2.36, U$2.37, U$2.40
